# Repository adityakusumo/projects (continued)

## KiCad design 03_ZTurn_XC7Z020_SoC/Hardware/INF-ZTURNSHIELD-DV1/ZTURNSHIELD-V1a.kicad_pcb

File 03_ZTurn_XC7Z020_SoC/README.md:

# LiteX SoC on MYIR Z-Turn (XC7Z020)

This project implements a LiteX-based SoC on the MYIR Z-Turn board, featuring a Xilinx Zynq-7000 (XC7Z020) SoC. It includes support for standard peripherals and specialized LVDS output.

## 📂 Project Structure

- **[Standard SoC](./Firmware/Litex/myir_xc7z020):** Base SoC implementation with standard peripherals.
- **[LVDS SoC](./Firmware/Litex/myir_xc7z020_lvds):** SoC implementation with LVDS display support.
- **[Hardware Reference](./Hardware):** Original schematics and shield design files.

## 🛠 Key Features

- **Platform:** Zynq-7000 XC7Z020.
- **Peripherals:** Temperature sensing (STLM75), LVDS Display.
- **Build System:** LiteX build scripts for easy gateware and firmware compilation.

## 🚀 Quick Start

To build and load the standard SoC:

```bash
cd Firmware/Litex/myir_xc7z020
./build_firmware.sh b  # Build gateware
./build_firmware.sh m  # Compile firmware
./build_firmware.sh l  # Load to SRAM
```

For more detailed workflows, refer to the README files in the respective firmware directories.

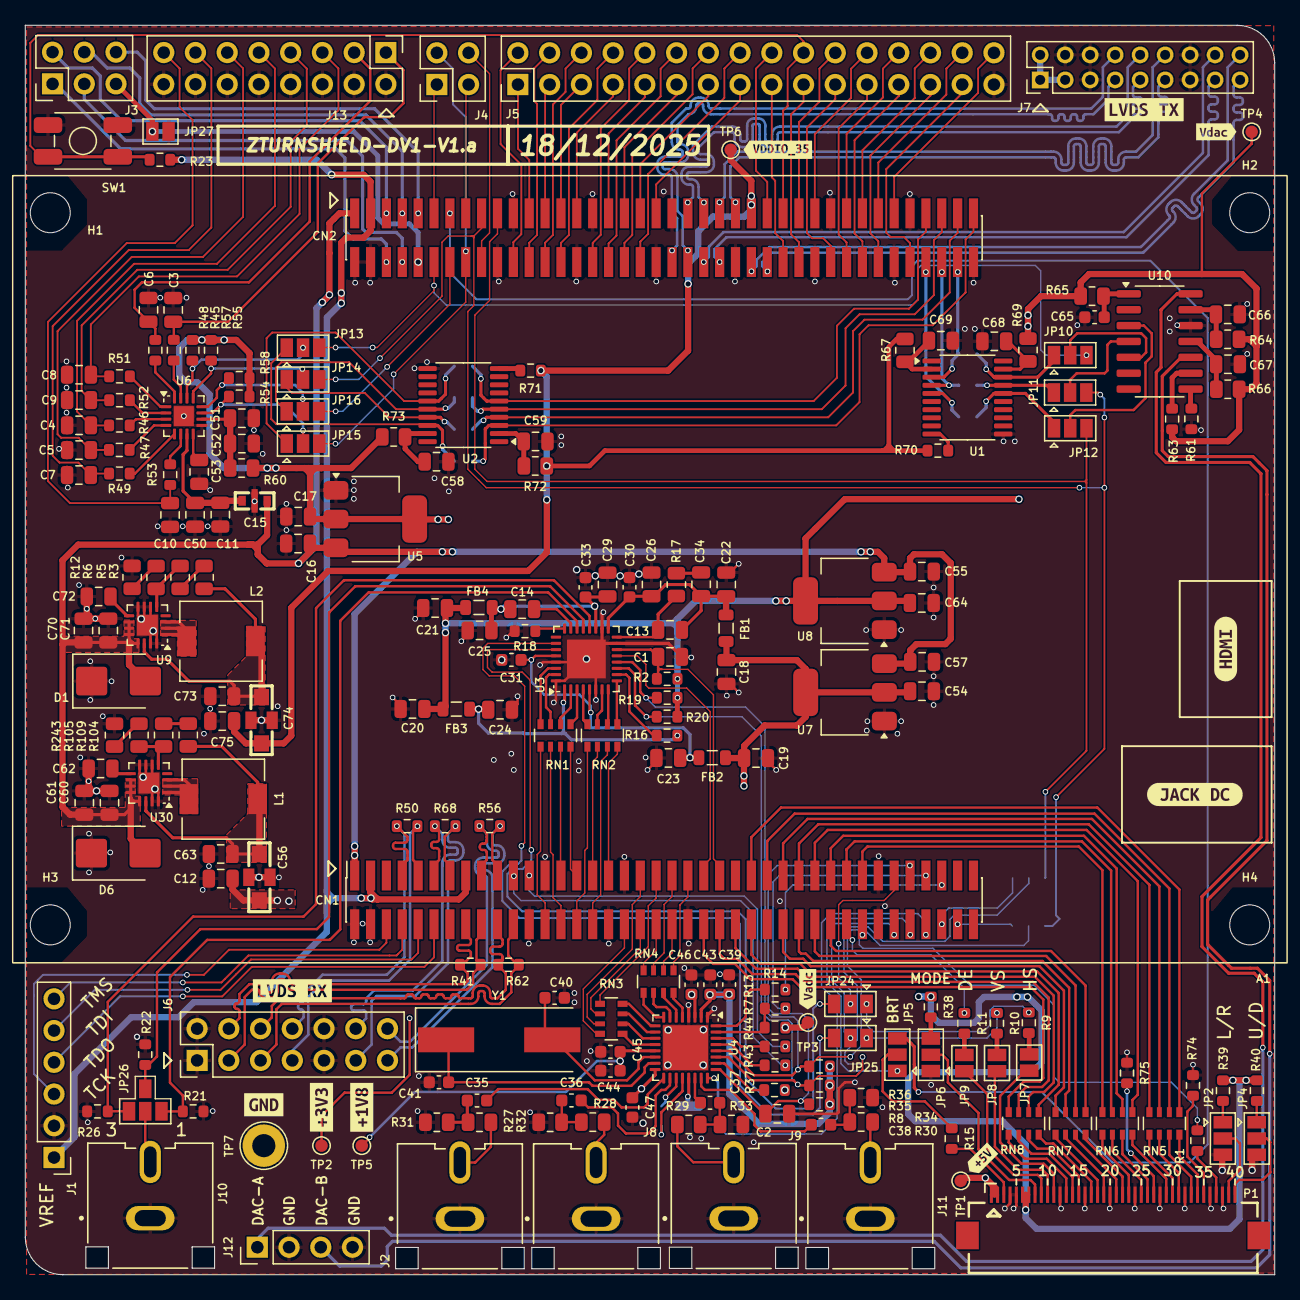
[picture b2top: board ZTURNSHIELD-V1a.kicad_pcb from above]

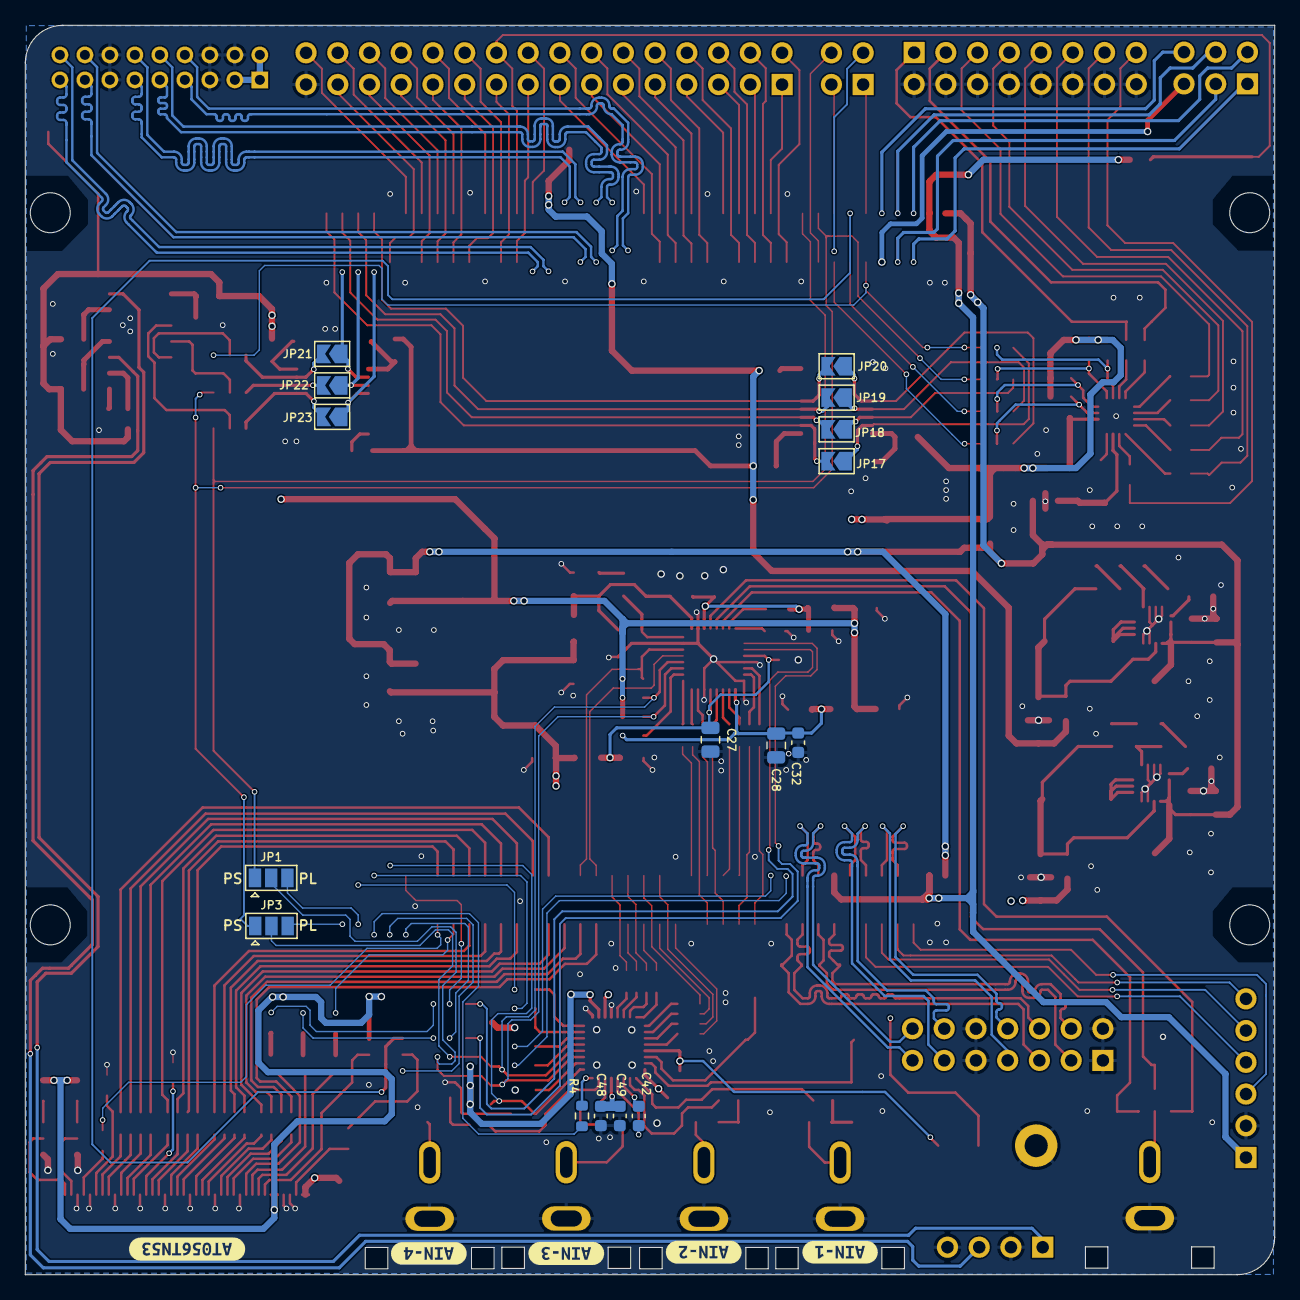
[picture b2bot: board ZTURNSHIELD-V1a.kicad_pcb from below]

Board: 4 copper layers, 100.0 x 100.0 mm, 250 parts (21 on the bottom side), 280 nets.

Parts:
A1: MYIR-ZTURN
C1, C12, C16, C26, C27, C28, C29, C55, C57, C58, C59, C61, C66, C67, C68, C69, C71, C75: 100nF; C_0805_2012Metric
C2: 4.7uF; C_0805_2012Metric
C3, C4, C5, C6, C7, C8, C9, C10, C11, C22, C23, C24, C25, C51, C53: 1uF; C_0805_2012Metric
C13, C34: 12nF; C_0805_2012Metric
C14: 2.2nF; C_0805_2012Metric
C15: Feedthrough; FILTER-SMD_4P-L2.0-W1.3-L_YFF21SC
C17, C18, C19, C20, C21, C54, C60, C64, C70: 10uF; C_0805_2012Metric
C30, C31, C32, C33, C43, C45, C46, C49: 10nF; C_0603_1608Metric
C35, C36, C37, C38, C39, C42, C44, C47, C48: 0,1uF; C_0603_1608Metric
C40, C41: 47pF; C_0603_1608Metric
C50, C52: 10nF; C_0805_2012Metric
C56, C74: Feedthrough; FILTER-SMD_4P-L3.2-W1.6-L_YFF31HC
C62, C72: 470pF; C_0805_2012Metric
C63, C73: 22uF; C_0805_2012Metric
C65: 100nF; C_0603_1608Metric
CN1, CN2: PinHeader_2x40_P1.27mm_Vertical_SMD_mirror
D1, D6: TVS_12V; D_SMB
FB1, FB2, FB3, FB4: Ferrite Bead; L_0805_2012Metric
H1, H2, H3, H4: MountingHole_Pad; MountingHole_3.2mm_M3_DIN965
J1: Jtag_01x06; PinHeader_1x06_P2.54mm_Vertical
J2, J8, J9, J10, J11: Conn_Coaxial; CUI_RCJ-044
J3: XADC_02x03_Odd_Even; PinHeader_2x03_P2.54mm_Vertical
J4: MIO_02x02_Odd_Even; PinHeader_2x02_P2.54mm_Vertical
J5: Conn_02x16_Odd_Even; PinHeader_2x16_P2.54mm_Vertical
J6: RxLvds_02x07_Odd_Even; PinHeader_2x07_P2.54mm_Vertical
J7: TxLvds_02x09_Odd_Even; PinHeader_2x09_P2.00mm_Vertical
J12: DAC_01x04; PinHeader_1x04_P2.54mm_Vertical
J13: ADC_02x08_Odd_Even; PinHeader_2x08_P2.54mm_Vertical
JP1, JP2, JP3, JP4, JP5, JP10, JP11, JP12, JP13, JP14, JP15, JP16, JP24, JP25: SolderJumper_3_Open; SolderJumper-3_P1.3mm_Open_Pad1.0x1.5mm
JP6: Jumper_NC_Dual; SolderJumper-3_P1.3mm_Open_Pad1.0x1.5mm
JP7, JP8, JP9, JP27: Jumper_NO_Small; SolderJumper-2_P1.3mm_Open_Pad1.0x1.5mm
JP17, JP18, JP19, JP20, JP21, JP22, JP23: SolderJumper_2_Open; SolderJumper-2_P1.3mm_Open_TrianglePad1.0x1.5mm
JP26: Jumper_4_Open; SolderJumper-4_P1.3mm_Open_Pad1.0x1.5mm_NumberLabels
L1, L2: 2u2; L_6.3x6.3_H3
P1: FH12-40S-0.5SH(55); FPC-SMD_FH12-40S-0.5SH-55
R1, R4, R9, R10, R11, R13, R14, R43, R44, R74, R75: 22R; R_0603_1608Metric
R2, R19, R20, R54, R61, R63, R70, R71: 10KR; R_0603_1608Metric
R3: 100KR; R_0805_2012Metric
R5, R12, R60, R64, R65, R66, R67, R69, R72, R73, R109, R243: 0R; R_0805_2012Metric
R6: 47KR; R_0805_2012Metric
R7, R8, R35, R36, R37, R38, R39, R40: 4K7R; R_0603_1608Metric
R15, R45, R46, R47, R48, R49, R51, R52, R53, R55, R57, R58: 1KR; R_0603_1608Metric
R16, R18: 510R; R_0603_1608Metric
R17: 160R; R_0805_2012Metric
R21, R22, R26: 75R; R_0603_1608Metric
R23: 100KR; R_0603_1608Metric
R27, R28, R29, R30: 24R; R_0805_2012Metric
R31, R32, R33, R34: 51R; R_0805_2012Metric
R41, R50, R56, R62, R68: 100R; R_0603_1608Metric
R104: 750KR; R_0805_2012Metric
R105: 240KR; R_0805_2012Metric
RN1, RN2, RN3, RN4, RN5, RN6, RN7, RN8: 22R; R_Array_Convex_4x0603
SW1: SW_Push; 7914G-1-000E
TP1, TP2, TP3, TP4, TP5, TP6: TestPoint; TestPoint_Pad_D1.0mm
TP7: TestPoint; TestPoint_Loop_D2.50mm_Drill1.85mm
U1, U2: TXS0108EPW; TSSOP-20_4.4x6.5mm_P0.65mm
U3: ADV7391BCPZ; LFCSP-32-1EP_5x5mm_P0.5mm_EP3.1x3.1mm
U4: ADV7280xCP; LFCSP-32-1EP_5x5mm_P0.5mm_EP3.6x3.6mm
U5, U8: LD1117S33TR_SOT223; SOT-223-3_TabPin2
U6: ADS7038; WQFN-16-1EP_3x3mm_P0.5mm_EP1.6x1.6mm
U7: LD1117S18CTR_SOT223; SOT-223-3_TabPin2
U9, U30: TLV62130RGTR; VQFN-16-1EP_3x3mm_P0.5mm_EP1.68x1.68mm
U10: MCP4922-EP; SOIC-14_3.9x8.7mm_P1.27mm
Y1: 28,6363Mhz; Crystal_SMD_HC49-SD
kibuzzard-694A5B5B: G***; kibuzzard-694A5B5B
kibuzzard-694A5B70: G***; kibuzzard-694A5B70
kibuzzard-694A5B85: G***; kibuzzard-694A5B85
kibuzzard-694A5BE1: G***; kibuzzard-694A5BE1
kibuzzard-694A5C9E: G***; kibuzzard-694A5C9E
kibuzzard-694A5CCC: G***; kibuzzard-694A5CCC
kibuzzard-694A5CD6: G***; kibuzzard-694A5CD6
kibuzzard-694A5CDB: G***; kibuzzard-694A5CDB
kibuzzard-694A5F29: G***; kibuzzard-694A5F29
kibuzzard-694A5F59: G***; kibuzzard-694A5F59
kibuzzard-694A5FF5: G***; kibuzzard-694A5FF5
kibuzzard-694A61D9: G***; kibuzzard-694A61D9
kibuzzard-694A61ED: G***; kibuzzard-694A61ED
kibuzzard-694A603D: G***; kibuzzard-694A603D
kibuzzard-694A668D: G***; kibuzzard-694A668D
kibuzzard-694A6013: G***; kibuzzard-694A6013

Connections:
+1V8: C18.1, C19.1, C44.1, C45.1, C46.1, C47.1, C48.1, C49.1, C54.1, FB1.1, FB2.1, TP5.1, U4.3 (DVDD), U4.13 (DVDD), U4.16 (PVDD), U4.21 (AVDD), U7.2 (VO)
+3.3VADC: C17.1, C39.1, C43.1, R7.1, R8.1, R35.1, R36.1, R37.1, R54.1, R55.1, R57.1, R58.1, R60.1, R73.1, TP3.1, U4.2 (DVDDIO), U5.2 (VO)
+3.3VDAC: C20.1, C21.1, C64.1, FB3.1, FB4.1, R2.2, R19.2, R20.2, R63.1, R64.1, R65.1, R66.2, R69.1, TP4.1, U8.2 (VO)
+3V3: C12.1, C56.3, J7.1, J7.2, J7.3, P1.6, P1.7, R38.1, R39.1, R40.1, TP2.1
/BlockDiagram/ADC/ADC_CS: JP15.2 (C), R54.2, U6.11 (CS)
/BlockDiagram/ADC/ADC_SCLK: JP14.2 (C), R55.2, U6.13 (SCLK)
/BlockDiagram/ADC/ADC_SDI: JP13.2 (C), R57.2, U6.14 (SDI)
/BlockDiagram/ADC/ADC_SDO: JP16.2 (C), R58.2, U6.12 (SDO)
/BlockDiagram/ADC/PL_ADC_CS: JP15.1 (A), JP20.1 (A), U2.15 (B5)
/BlockDiagram/ADC/PL_ADC_MISO: JP16.1 (A), JP19.1 (A), U2.16 (B4)
/BlockDiagram/ADC/PL_ADC_MOSI: JP13.1 (A), JP17.1 (A), U2.18 (B2)
/BlockDiagram/ADC/PL_ADC_SCK: JP14.1 (A), JP18.1 (A), U2.17 (B3)
/BlockDiagram/DAC/DAC_CS: JP12.2 (C), U10.3 (~CS)
/BlockDiagram/DAC/DAC_MOSI: JP10.2 (C), U10.5 (SDI)
/BlockDiagram/DAC/DAC_SCK: JP11.2 (C), U10.4 (SCK)
/BlockDiagram/DAC/PL_DAC_CS: JP12.1 (A), JP23.2 (B), U1.16 (B4)
/BlockDiagram/DAC/PL_DAC_MOSI: JP10.1 (A), JP21.2 (B), U1.18 (B2)
/BlockDiagram/DAC/PL_DAC_SCK: JP11.1 (A), JP22.2 (B), U1.17 (B3)
/BlockDiagram/LCD_CTRL/ADJ_BR: P1.3, R15.2
/BlockDiagram/LCD_CTRL/B0: P1.19, RN7.6 (R3.2)
/BlockDiagram/LCD_CTRL/B1: P1.18, RN7.5 (R4.2)
/BlockDiagram/LCD_CTRL/B2: P1.17, RN8.8 (R1.2)
/BlockDiagram/LCD_CTRL/B3: P1.15, RN8.7 (R2.2)
/BlockDiagram/LCD_CTRL/B4: P1.14, RN8.6 (R3.2)
/BlockDiagram/LCD_CTRL/B5: P1.13, RN8.5 (R4.2)
/BlockDiagram/LCD_CTRL/DCLK: P1.37, R1.2
/BlockDiagram/LCD_CTRL/DE: JP9.2, R11.2
/BlockDiagram/LCD_CTRL/DE_O: JP9.1, P1.9
/BlockDiagram/LCD_CTRL/G0: P1.27, R75.2
/BlockDiagram/LCD_CTRL/G1: P1.26, RN6.7 (R2.2)
/BlockDiagram/LCD_CTRL/G2: P1.25, RN6.6 (R3.2)
/BlockDiagram/LCD_CTRL/G3: P1.23, RN6.5 (R4.2)
/BlockDiagram/LCD_CTRL/G4: P1.22, RN7.8 (R1.2)
/BlockDiagram/LCD_CTRL/G5: P1.21, RN7.7 (R2.2)
/BlockDiagram/LCD_CTRL/HS: JP7.2, R9.2
/BlockDiagram/LCD_CTRL/HS_O: JP7.1, P1.11
/BlockDiagram/LCD_CTRL/L\R: JP2.2 (C), P1.39
/BlockDiagram/LCD_CTRL/MODE: JP6.2, P1.8
/BlockDiagram/LCD_CTRL/R0: P1.35, R74.2
/BlockDiagram/LCD_CTRL/R1: P1.34, RN5.8 (R1.2)
/BlockDiagram/LCD_CTRL/R2: P1.33, RN5.7 (R2.2)
/BlockDiagram/LCD_CTRL/R3: P1.31, RN5.6 (R3.2)
/BlockDiagram/LCD_CTRL/R4: P1.30, RN5.5 (R4.2)
/BlockDiagram/LCD_CTRL/R5: P1.29, RN6.8 (R1.2)
/BlockDiagram/LCD_CTRL/U\D: JP4.2 (C), P1.40
/BlockDiagram/LCD_CTRL/VS: JP8.2, R10.2
/BlockDiagram/LCD_CTRL/VS_O: JP8.1, P1.10
/BlockDiagram/VIDEO_ENCODER/PVDD: C13.2, C22.1, C26.1, C30.1, C34.2, FB1.2, U3.17 (PVDD)
/BlockDiagram/VIDEO_ENCODER/VAA: C14.1, C25.1, C29.1, C33.1, FB4.2, U3.19 (VAA)
/BlockDiagram/VIDEO_ENCODER/VDD_IO: C24.1, C28.1, C32.1, FB3.2, R16.1, U3.1 (VDD_IO)
ADV7280_HS: R44.2, U4.30 (HS)
ADV7280_INTRQ: R4.2, U4.24 (~INTRQ)
ADV7280_LLC: R14.2, U4.32 (LLC)
ADV7280_PWRDWN: R7.2, R13.2, U4.31 (~PWRDWN)
ADV7280_RESET: C2.1, CN1.71, R8.2, U4.25 (~RESET)
ADV7280_VS/SFL/FIELD: R43.2, U4.29 (VS/FIELD/SFL)
ADV7391_ADC1: JP26.1, R21.2, U3.22 (DAC1)
ADV7391_ADC2: JP26.2, R22.2, U3.21 (DAC2)
ADV7391_ADC3: JP26.3, R26.2, U3.20 (DAC3)
ADV7391_CLKIN: CN1.45, U3.13 (CLKIN)
ADV7391_RESET: C1.1, CN1.47, R2.1, U3.14 (*RESET)
ADV7391_SCL: JP3.2 (C), R19.1, R36.2, U3.12 (SCL), U4.28 (SCLK)
ADV7391_SDA: JP1.2 (C), R20.1, R35.2, U3.11 (SDA), U4.27 (SDATA)
AIN0: C3.1, J13.1, R45.1
AIN1: C6.1, J13.3, R48.1
AIN2: C8.1, J13.5, R51.1
AIN3: C9.1, J13.7, R52.1
AIN4: C4.1, J13.9, R46.1
AIN5: C5.1, J13.11, R47.1
AIN6: C7.1, J13.13, R49.1
AIN7: C10.1, J13.15, R53.1
DAC_OUT_A: J12.1, U10.14 (VoutA)
DAC_OUT_B: J12.3, U10.10 (VoutB)
GND: C1.2, C2.2, C3.2, C4.2, C5.2, C6.2, C7.2, C8.2, C9.2, C10.2, C11.2, C12.2, C15.2, C15.4 (2), C16.2, C17.2, C18.2, C19.2, C20.2, C21.2, C22.2, C23.2, C24.2, C25.2, C26.2, C27.2, C28.2, C29.2, C30.2, C31.2, C32.2, C33.2, C39.2, C40.1, C41.1, C43.2, C44.2, C45.2, C46.2, C47.2, C48.2, C49.2, C50.2, C51.2, C52.2, C53.2, C54.2, C55.2, C56.2, C56.4 (2), C57.2, C58.2, C59.2, C60.2, C61.1, C62.2, C63.2, C64.2, C65.2, C66.2, C67.2, C68.2, C69.2, C70.2, C71.1, C72.2, C73.2, C74.2, C74.4 (2), C75.2, CN1.2, CN1.4, CN1.24, CN1.25, CN1.34, CN1.35, CN1.44, CN1.54, CN1.67, CN1.68, CN2.2, CN2.4, CN2.20, CN2.21, CN2.30, CN2.31, CN2.40, CN2.41, CN2.50, CN2.60, CN2.61, CN2.70, CN2.71, CN2.80, D1.1 (A1), D6.1 (A1), J1.2, J2.2 (Ext), J5.31, J6.1, J6.2, J6.9, J6.10, J7.4, J7.5, J7.6, J7.13, J7.14, J8.2 (Ext), J9.2 (Ext), J10.2 (Ext), J11.2 (Ext), J12.2, J12.4, J13.2, J13.4, J13.6, J13.8, J13.10, J13.12, J13.14, J13.16, JP2.3 (B), JP4.3 (B), JP6.1, JP27.2, P1.4, P1.5, P1.12, P1.16, P1.20, P1.24, P1.28, P1.32, P1.36, P1.38, R12.2, R18.1, R21.1, R22.1, R26.1, R31.1, R32.1, R33.1, R34.1, R61.1, R74.1, R75.1, R243.2, SW1.1, TP7.1, U1.11 (GND), U2.11 (GND), U3.6 (DGND_2), U3.15 (PGND), U3.18 (AGND), U3.29 (DGND), U3.32 (GND_IO), U3.33 (EP), U4.1 (DGND), U4.4 (DGND), U4.33 (DGND), U5.1 (GND), U6.9 (GND), U6.17 (GND), U7.1 (GND), U8.1 (GND), U9.6 (AGND), U9.7 (FSW), U9.8 (DEF), U9.15 (PGND1), U9.16 (PGND2), U9.17 (TPAD), U10.12 (AVSS), U30.6 (AGND), U30.7 (FSW), U30.8 (DEF), U30.15 (PGND1), U30.16 (PGND2), U30.17 (TPAD)
I2S_DIN: CN1.75, R14.1
I2S_DOUT: CN1.74, R4.1
I2S_FSYNC_IN: CN1.73, R13.1
I2S_FSYNC_OUT: CN1.72, JP5.1 (A)
IO_B13_LN11: CN1.9, J6.7, R50.2
IO_B13_LN12: CN1.13, J6.11, R68.2
IO_B13_LN13: CN1.19, J6.13, R56.2
IO_B13_LN14: CN1.18, J6.3, R41.2
IO_B13_LN15: CN1.23, R44.1
IO_B13_LN21: CN1.22, J6.5, R62.2
IO_B13_LP11: CN1.7, J6.8, R50.1
IO_B13_LP12: CN1.11, J6.12, R68.1
IO_B13_LP13: CN1.17, J6.14, R56.1
IO_B13_LP14: CN1.16, J6.4, R41.1
IO_B13_LP15: CN1.21, R43.1
IO_B13_LP21: CN1.20, J6.6, R62.1
IO_B34_LN1: CN1.28, RN1.6 (R3.2)
IO_B34_LN2: CN1.29, RN1.8 (R1.2)
IO_B34_LN3: CN1.32, RN2.7 (R2.2)
IO_B34_LN4: CN1.33, RN2.8 (R1.2)
IO_B34_LN5: CN1.38, RN3.2 (R2.1)
IO_B34_LN6: CN1.39, RN3.1 (R1.1)
IO_B34_LN7: CN1.42, RN4.2 (R2.1)
IO_B34_LN8: CN1.43, RN4.1 (R1.1)
IO_B34_LP1: CN1.26, RN1.5 (R4.2)
IO_B34_LP2: CN1.27, RN1.7 (R2.2)
IO_B34_LP3: CN1.30, RN2.5 (R4.2)
IO_B34_LP4: CN1.31, RN2.6 (R3.2)
IO_B34_LP5: CN1.36, RN3.4 (R4.1)
IO_B34_LP6: CN1.37, RN3.3 (R3.1)
IO_B34_LP7: CN1.40, RN4.4 (R4.1)
IO_B34_LP8: CN1.41, RN4.3 (R3.1)
IO_B35_LN1: CN2.25, J5.3
IO_B35_LN2: CN2.24, J5.4
IO_B35_LN3: CN2.29, J5.7
IO_B35_LN4: CN2.28, J5.8
IO_B35_LN5: CN2.35, J5.11
IO_B35_LN6: CN2.34, J5.12
IO_B35_LN7: CN2.39, J5.15
IO_B35_LN8: CN2.38, J5.16
IO_B35_LN9: CN2.45, J7.9
IO_B35_LN10: CN2.44, J7.7
IO_B35_LN11: CN2.49, J7.11
IO_B35_LN12: CN2.48, J7.15
IO_B35_LN13: CN2.55, J5.20, R23.2, SW1.2
IO_B35_LN14: CN2.54, J7.17
IO_B35_LN15: CN2.59, J5.24
IO_B35_LN16: CN2.58, J5.19
IO_B35_LN17: CN2.65, J5.28
IO_B35_LN18: CN2.64, J5.23
IO_B35_LN19: CN2.69, J5.32
IO_B35_LN20: CN2.68, J5.27
IO_B35_LN21: CN2.75, JP19.2 (B), U2.5 (A4)
IO_B35_LN22: CN2.74, JP23.1 (A), U1.5 (A4)
IO_B35_LN23: CN2.79, JP17.2 (B), U2.3 (A2)
IO_B35_LN24: CN2.78, JP21.1 (A), U1.3 (A2)
IO_B35_LP1: CN2.23, J5.1
IO_B35_LP2: CN2.22, J5.2
IO_B35_LP3: CN2.27, J5.5
IO_B35_LP4: CN2.26, J5.6
IO_B35_LP5: CN2.33, J5.9
IO_B35_LP6: CN2.32, J5.10
IO_B35_LP7: CN2.37, J5.13
IO_B35_LP8: CN2.36, J5.14
IO_B35_LP9: CN2.43, J7.10
IO_B35_LP10: CN2.42, J7.8
IO_B35_LP11: CN2.47, J7.12
IO_B35_LP12: CN2.46, J7.16
IO_B35_LP13: CN2.53, J5.18
IO_B35_LP14: CN2.52, J7.18
IO_B35_LP15: CN2.57, J5.22
IO_B35_LP16: CN2.56, J5.17
IO_B35_LP17: CN2.63, J5.26
IO_B35_LP18: CN2.62, J5.21
IO_B35_LP19: CN2.67, J5.30
IO_B35_LP20: CN2.66, J5.25
IO_B35_LP21: CN2.73, JP20.2 (B), U2.6 (A5)
IO_B35_LP22: CN2.72, J5.29
IO_B35_LP23: CN2.77, JP18.2 (B), U2.4 (A3)
IO_B35_LP24: CN2.76, JP22.1 (A), U1.4 (A3)
JTAG_TCK: CN1.6, J1.3
JTAG_TDI: CN1.10, J1.5
JTAG_TDO: CN1.12, J1.4
JTAG_TMS: CN1.8, J1.6
LCD_DATA0: CN1.51, RN5.1 (R1.1)
LCD_DATA1: CN1.53, RN5.2 (R2.1)
LCD_DATA2: CN1.46, RN8.4 (R4.1)
LCD_DATA3: CN1.48, RN8.3 (R3.1)
LCD_DATA4: CN1.55, RN5.3 (R3.1)
LCD_DATA5: CN1.57, RN5.4 (R4.1)
LCD_DATA6: CN1.50, RN8.2 (R2.1)
LCD_DATA7: CN1.52, RN8.1 (R1.1)
LCD_DATA8: CN1.59, RN6.1 (R1.1)
LCD_DATA9: CN1.61, RN6.2 (R2.1)
LCD_DATA10: CN1.56, RN7.4 (R4.1)
LCD_DATA11: CN1.58, RN7.3 (R3.1)
LCD_DATA12: CN1.63, RN6.3 (R3.1)
LCD_DATA13: CN1.65, RN6.4 (R4.1)
LCD_DATA14: CN1.60, RN7.2 (R2.1)
LCD_DATA15: CN1.62, RN7.1 (R1.1)
LCD_DE: CN1.64, R11.1
LCD_HSINYC: CN1.69, JP24.2 (C)
LCD_PCLK: CN1.66, R1.1
LCD_VSINYC: CN1.70, JP25.2 (C)
unnamed: C34.1, R17.1
unnamed: C35.1, R27.2, R31.2
unnamed: C36.1, R28.2, R32.2
unnamed: C36.2, U4.18 (AIN2)
unnamed: C37.1, R29.2, R33.2
unnamed: C37.2, U4.22 (AIN2)
unnamed: C38.1, R30.2, R34.2
unnamed: J10.1 (In), JP26.4 (Common)
unnamed: JP2.1 (A), R39.2
unnamed: JP4.1 (A), R40.2
unnamed: JP5.2 (C), R15.1
unnamed: JP6.3, R38.2
unnamed: R3.2, R5.1
unnamed: R6.2, R12.1
unnamed: R104.2, R109.1
unnamed: R105.2, R243.1
unnamed: RN1.1 (R1.1), U3.3
unnamed: RN1.2 (R2.1), U3.2
unnamed: RN1.3 (R3.1), U3.31 (P1)
unnamed: RN1.4 (R4.1), U3.30 (P0)
unnamed: RN2.1 (R1.1), U3.9 (P7)
unnamed: RN2.2 (R2.1), U3.8 (P6)
unnamed: RN2.3 (R3.1), U3.7 (P5)
unnamed: RN2.4 (R4.1), U3.4
unnamed: RN3.8 (R1.2), U4.9 (P3)
unnamed: RN3.7 (R2.2), U4.10 (P2)
unnamed: RN3.6 (R3.2), U4.11 (P1)
unnamed: RN3.5 (R4.2), U4.12 (P0)
unnamed: RN4.8 (R1.2), U4.5 (P7)
unnamed: RN4.7 (R2.2), U4.6
unnamed: RN4.6 (R3.2), U4.7 (P5)
unnamed: RN4.5 (R4.2), U4.8 (P4)
unnamed: R70.2, U1.10 (OE)
unnamed: C69.1, R67.2, U1.2 (VCCA)
unnamed: C68.1, R69.2, U1.19 (VCCB)
unnamed: R71.2, U2.10 (OE)
unnamed: C59.1, R72.2, U2.2 (VCCA)
unnamed: C58.1, R73.2, U2.19 (VCCB)
unnamed: R16.2, U3.10 (ALSB)
unnamed: C14.2, U3.23 (COMP)
unnamed: C13.1, R17.2, U3.16 (EXT_LF)
unnamed: R18.2, U3.24 (RSET)
unnamed: C23.1, C27.1, C31.1, FB2.2, U3.5 (VDD_), U3.28 (VDD)
unnamed: C35.2, U4.17 (AIN1)
unnamed: C38.2, U4.23 (AIN3)
unnamed: R37.2, U4.26 (ALSB)
unnamed: C42.2, U4.20 (VREFN)
unnamed: C42.1, U4.19 (VREFP)
unnamed: C41.2, U4.15 (XTALN), Y1.1
unnamed: C40.2, U4.14 (XTALP), Y1.2
unnamed: R45.2, U6.15 (AIN0)
unnamed: R48.2, U6.16 (AIN1)
unnamed: R51.2, U6.1 (AIN2)
unnamed: R52.2, U6.2 (AIN3)
unnamed: R46.2, U6.3 (AIN4)
unnamed: R47.2, U6.4 (AIN5)
unnamed: R49.2, U6.5 (AIN6)
unnamed: R53.2, U6.6 (AIN7)
unnamed: C11.1, C15.1, C50.1, U6.7 (AVDD)
unnamed: C53.1, U6.8 (DECAP)
unnamed: C51.1, C52.1, R60.2, U6.10 (DVDD)
unnamed: R5.2, R6.1, U9.5 (FB)
unnamed: C72.1, U9.9 (SS/TR)
unnamed: L2.1, U9.1 (SW1), U9.2 (SW2), U9.3 (SW3)
unnamed: C73.1, C74.1, L2.2, R3.1, U9.14 (VOS)
unnamed: C65.1, R65.2, U10.1 (VDD)
unnamed: C66.1, R64.2, U10.13 (VrefA)
unnamed: C67.1, R66.1, U10.11 (VrefB)
unnamed: R61.2, U10.8 (~LDAC)
unnamed: R63.2, U10.9 (~SHDN)
unnamed: R105.1, R109.2, U30.5 (FB)
unnamed: C62.1, U30.9 (SS/TR)
unnamed: L1.1, U30.1 (SW1), U30.2 (SW2), U30.3 (SW3)
unnamed: C56.1, C63.1, L1.2, R104.1, U30.14 (VOS)
PAL_HSYNC: JP24.3 (B), U3.27 (*HSYNC)
PAL_VSYNC: JP25.3 (B), U3.26 (*VSYNC)
PL_I2C_SCL: CN1.78, JP3.3 (B)
PL_I2C_SDA: CN1.76, JP1.3 (B)
PS_MIO0: CN2.11, J4.1
PS_MIO8: CN2.13, JP5.3 (B)
PS_MIO9: CN2.15, J4.3
PS_MIO10: CN2.12, JP10.3 (B), JP13.3 (B)
PS_MIO11: CN2.14, JP16.3 (B)
PS_MIO12: CN2.17, JP3.1 (A), JP11.3 (B), JP14.3 (B)
PS_MIO13: CN2.19, JP1.1 (A), JP12.3 (B)
PS_MIO14: CN2.16, J4.2, JP15.3 (B)
PS_MIO15: CN2.18, J4.4
TFT_HSYNC: JP24.1 (A), R9.1
TFT_VSYNC: JP25.1 (A), R10.1
VDDIO_35: C74.3, C75.1, CN2.51, R67.1, R70.1, R71.1, R72.1, TP6.1
VDD_3V3: CN1.3, CN1.15, CN2.3, J1.1, R23.1
VDD_5V: C15.3, C16.1, C55.1, C57.1, C60.1, C61.2, C70.1, C71.2, CN1.1, CN2.1, D1.2 (A2), D6.2 (A2), P1.1, P1.2, TP1.1, U5.3 (VI), U7.3 (VI), U8.3 (VI), U9.10 (AVIN), U9.11 (PVIN1), U9.12 (PVIN2), U9.13 (EN), U30.10 (AVIN), U30.11 (PVIN1), U30.12 (PVIN2), U30.13 (EN)
VIDDEC_AIN1: J2.1 (In), R27.1
VIDDEC_AIN2: J8.1 (In), R28.1
VIDDEC_AIN3: J9.1 (In), R29.1
VIDDEC_AIN4: J11.1 (In), R30.1
XADC_GND: CN2.10, J3.5, JP27.1
XADC_INN0: CN2.7, J3.4
XADC_INP0: CN2.5, J3.2
XADC_TEMP_N: CN2.8, J3.3
XADC_TEMP_P: CN2.6, J3.1
XADC_VCC: CN2.9, J3.6

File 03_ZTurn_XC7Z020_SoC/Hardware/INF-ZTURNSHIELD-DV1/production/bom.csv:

Designator,Footprint,Quantity,Value,LCSC Part #
A1,MYIR-ZTURN,1,~,
"C1, C26, C27, C28, C29, C58, C59, C66, C67, C68, C69",0805,11,100nF,
"C10, C11, C22, C23, C24, C25, C3, C4, C5, C51, C53, C6, C7, C8, C9",0805,15,1uF,
"C12, C16, C55, C57, C61, C71, C75",0805,7,100nF,CL21B104KBFNNNG
"C13, C34",0805,2,12nF,
C14,0805,1,2.2nF,
C15,FILTER-SMD_4P-L2.0-W1.3-L_YFF21SC,1,Feedthrough,C2650914
"C17, C54, C64",0805,3,10uF,C2012X5R1C226M085AC
"C18, C19, C20, C21",0805,4,10uF,
C2,0805,1,4.7uF,
"C30, C31, C32, C33, C43, C45, C46, C49",0603,8,10nF,
"C35, C36, C37, C38, C39, C42, C44, C47, C48",0603,9,"0,1uF",
"C40, C41",0603,2,47pF,
"C50, C52",0805,2,10nF,
C56,FILTER-SMD_4P-L3.2-W1.6-L_YFF31HC,1,Feedthrough,C2650930
"C60, C70",0805,2,10uF,CL21Y106KOBVPNE
"C62, C72",0805,2,470pF,C0805C471K5RACTU
"C63, C73",0805,2,22uF,C2012X5R1C226M085AC
C65,0603,1,100nF,
"CN1, CN2",PinHeader_2x40_P1.27mm_Vertical_SMD_mirror,2,~,
"D1, D6",D_SMB,2,TVS_12V,SMBJ12CA
"FB1, FB2, FB3, FB4",0805,4,Ferrite Bead,
J1,PinHeader_1x06_P2.54mm_Vertical,1,Jtag_01x06,
"J10, J11, J2, J8, J9",CUI_RCJ-044,5,Conn_Coaxial,
J12,PinHeader_1x04_P2.54mm_Vertical,1,DAC_01x04,
J13,PinHeader_2x08_P2.54mm_Vertical,1,ADC_02x08_Odd_Even,
J3,PinHeader_2x03_P2.54mm_Vertical,1,XADC_02x03_Odd_Even,
J4,PinHeader_2x02_P2.54mm_Vertical,1,MIO_02x02_Odd_Even,
J5,PinHeader_2x16_P2.54mm_Vertical,1,Conn_02x16_Odd_Even,
J6,PinHeader_2x07_P2.54mm_Vertical,1,RxLvds_02x07_Odd_Even,
J7,PinHeader_2x09_P2.00mm_Vertical,1,TxLvds_02x09_Odd_Even,
"JP2, JP4",SolderJumper-3_P1.3mm_Open_Pad1.0x1.5mm,2,SolderJumper_3_Open,
JP26,SolderJumper-4_P1.3mm_Open_Pad1.0x1.5mm_NumberLabels,1,Jumper_4_Open,
"JP27, JP7, JP8, JP9",SolderJumper-2_P1.3mm_Open_Pad1.0x1.5mm,4,Jumper_NO_Small,
JP6,SolderJumper-3_P1.3mm_Open_Pad1.0x1.5mm,1,Jumper_NC_Dual,
"L1, L2",L_6.3x6.3_H3,2,2u2,IHLP2020CZER2R2M8A
P1,FPC-SMD_FH12-40S-0.5SH-55,1,FH12-40S-0.5SH(55),C202114
"R1, R10, R11, R13, R14, R4, R43, R44, R74, R75, R9",0603,11,22R,
R104,0805,1,750KR,CR0805-FX-7503ELF
R105,0805,1,240KR,CR0805-JW-244ELF
"R109, R12, R243, R5",0805,4,0R,RC0805JR-070RL
"R15, R45, R46, R47, R48, R49, R51, R52, R53",0603,9,1KR,
"R16, R18",0603,2,510R,
R17,0805,1,160R,
"R2, R54, R61, R63, R70, R71",0603,6,10KR,
"R21, R22, R26",0603,3,75R,
R23,0603,1,100KR,
"R27, R28, R29, R30",0805,4,24R,
R3,0805,1,100KR,CR0805-FX-7503ELF
"R31, R32, R33, R34",0805,4,51R,
"R37, R38, R39, R40, R7, R8",0603,6,4K7R,
"R41, R50, R56, R62, R68",0603,5,100R,
R6,0805,1,47KR,CR0805-JW-244ELF
"R60, R64, R65, R66, R67, R69, R72, R73",0805,8,0R,
"RN1, RN2, RN3, RN4",R_Array_Convex_4x0603,4,22R,
"RN5, RN6, RN7, RN8",R_Array_Convex_4x0603,4,22R,
SW1,7914G-1-000E,1,SW_Push,
"TP1, TP2, TP3, TP4, TP5, TP6",TestPoint_Pad_D1.0mm,6,TestPoint,
TP7,TestPoint_Loop_D2.50mm_Drill1.85mm,1,TestPoint,
"U1, U2",TSSOP-20_4.4x6.5mm_P0.65mm,2,TXS0108EPW,
U10,SOIC-14_3.9x8.7mm_P1.27mm,1,MCP4922-EP,
U3,LFCSP-32-1EP_5x5mm_P0.5mm_EP3.1x3.1mm,1,ADV7391BCPZ,ADV7391BCPZ
"U30, U9",VQFN-16-1EP_3x3mm_P0.5mm_EP1.68x1.68mm,2,TLV62130RGTR,TLV62130RGTR
U4,LFCSP-32-1EP_5x5mm_P0.5mm_EP3.6x3.6mm,1,ADV7280xCP,C662254
"U5, U8",SOT-223-3_TabPin2,2,LD1117S33TR_SOT223,
U6,WQFN-16-1EP_3x3mm_P0.5mm_EP1.6x1.6mm,1,ADS7038,
U7,SOT-223-3_TabPin2,1,LD1117S18CTR_SOT223,
Y1,Crystal_SMD_HC49-SD,1,"28,6363Mhz",

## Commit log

2026-01-07 Add first stcc litex project
2026-01-07 Add root gitignore
2026-01-07 Add STCC pcb design
2026-01-07 Update stcc litex firmware
    add CSR for connecting between migen with firmware and viceversa
2026-01-08 Add Litex with Ise example project
2026-01-08 Update readme and add VGA gif
2026-01-08 Update litex ise readme
    edit gif url
2026-01-08 Update litex ise readme
    add new line
2026-01-08 Update litex-ise soc.py
    add more description for CSR
2026-01-08 Update litex-ise ISE file
    add push button input
2026-01-08 Update litex-ise litex code
    add push button and csr button
2026-01-09 Update litex-ise project
    add led controller in separate .py file
2026-01-09 Add readme for simulation
2026-01-09 Add DDR Test Project
2026-03-02 Add new project - CMFD 10.4 inch
2026-03-02 Update gitignore
    add xilinx ise ignore file
2026-03-02 Update firmware - CMFD 10.4 litex
    add all2 command to .sh script
2026-03-02 Update firmware - CMFD 10.4 litex clk freq
    add PLL_BASE for dividing clock from 50mhz to 40mhz
2026-03-02 Add firmware - litex stcc1 lx25 board
2026-03-02 Update firmware - CMFD 10.4 litex
    add lvds transmit module
2026-03-03 Add firmware - litex vga to lvds
2026-03-03 Update firmware - cmfd 10 litex lvds rainbow generator
    commented out bist_o = 0
2026-03-04 Update gitignore
    ignore vcd file - this file has a huge size if the simulation is complex
2026-03-04 Update firmware litex - vga2lvds
    generates internal vga signal using video.py function and convert it to
    lvds
2026-03-04 Update firmware litex - cmfd 10.4
    edit the clock comment from 50mhz to 80mhz
2026-03-05 Update cmfd10.4 firmware
    add both ISE and Litex project
    update readme file
2026-03-09 Add litex firmware - vga2lvds with ddr test
2026-03-17 Add Myir Zynq Project
2026-03-17 Update Myir - firmware litex
    update build_firmware.sh file to include simulation command
2026-03-30 Add Qmtech Artix 7 wukong board
2026-03-30 Update gitignore file for litex
2026-03-30 Update wukong board firmware
2026-05-06 Re-structure git repo
